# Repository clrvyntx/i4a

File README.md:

# ComNetAR: ESP32 Ring Network Connection Project

## Project Overview

This project implements a ring network topology using ESP32 microcontrollers connected via SPI (Serial Peripheral Interface). Each ESP32 board functions simultaneously as an SPI master and slave, creating a circular communication chain where data can flow bidirectionally through the network. This architecture enables efficient local communication within IoT nodes, supporting configurations from 2 to 5 boards in a single ring.

The system's unique feature is its dual-role approach: each board acts as a master for the next board and a slave for the previous one, enabling seamless data transmission throughout the network. One of the boards serves as an Access Point (AP), allowing the node to communicate with external networks while maintaining internal ring communication.

## Compatible Hardware
This project has been tested and verified to work with the following ESP32 boards:

- Espressif ESP32-DevKitC v4 (https://docs.espressif.com/projects/esp-idf/en/v5.1/esp32/hw-reference/esp32/get-started-devkitc.html#)

### Pinout

While the project may work with other ESP32 boards that have similar specifications, compatibility cannot be guaranteed without testing.

## Prerequisites

### ESP-IDF Installation
Before starting with this project, you need to install ESP-IDF v5.1.2. Follow these steps:

1. **Windows Installation**:
   - Download the ESP-IDF Windows Installer from the official ESP-IDF Releases page
   - Run the installer and follow the installation wizard
   - The installer will download and install:
     * ESP-IDF tools
     * Git
     * Python
     * Required build tools

2. **Linux/macOS Installation**:
   ```bash
   mkdir -p ~/esp
   cd ~/esp
   git clone -b v5.1.2 --recursive https://github.com/espressif/esp-idf.git
   cd esp-idf
   ./install.sh
   ```

3. **Set up ESP-IDF environment variables**:
   - Windows: Run `C:\esp\esp-idf\export.bat`
   - Linux/macOS: `. ~/esp/esp-idf/export.sh`

For detailed installation instructions, visit [ESP-IDF Get Started Guide](https://docs.espressif.com/projects/esp-idf/en/v5.1.2/esp32/get-started/index.html)

## Installing and Building the Project

1. Clone this repo and cd into it:
   ```bash
   git clone https://github.com/clrvyntx/i4a
   cd i4a
   ```

2. Set up the ESP-IDF environment:
   ```bash
   get_idf
   ```

3. Build the project:
   ```bash
   idf.py build
   ```
   Note: Initial build will take some time while it compiles all required libraries.

## Board Configuration Options

The system supports between 2 to 5 ESP32 boards in a ring configuration:

### Possible Setups:
1. **2 boards**: Minimal configuration
   - Each ESP32 acts as both master and slave
   - Direct bidirectional communication

2. **3-4 boards**: Intermediate configuration

   Forms a ring where each board connects to its neighbors
   Required boards:

   One AP (Access Point) board
   Two or three boards from: North, South, East, or West

   Example (3 boards): AP + North + South
   Example (4 boards): AP + North + South + East

3. **5 boards**: Full configuration
   - Complete board setup with all roles:
     * North board
     * South board
     * East board
     * West board
     * AP (Access Point) board

### Board Roles
Each ESP32 in the ring must be configured with its specific role using the configuration pins (see GPIO Configuration section).

## GPIO - Connections for ESP32 - Physical ports ring connections

```
Master Device          Slave Device
-------------         -------------
GPIO 23 (MOSI)  ────► GPIO 13 (MOSI)
GPIO 18 (SCLK)  ────► GPIO 14 (SCLK)
GPIO 5  (CS)    ────► GPIO 15 (CS)
```

#### Role Configuration System
**Configuration Pins (Pull-Up):**
- CONFIG_PIN_0: GPIO 22 (least significant bit)
- CONFIG_PIN_1: GPIO 21
- CONFIG_PIN_2: GPIO 16 (most significant bit)

## IDF configuration: sdkconfig file

```bash
   get_idf menuconfig
```

Variables:
```
CONFIG_LWIP_L2_TO_L3_COPY=y (Enable copy between Layer2 and Layer3 packets)
CONFIG_LWIP_IP_FORWARD=y (Enable IP forwarding)
LWIP_IP_DEBUG=y (Only for debug)
```

## ESP32 Component Testing Guide

This guide explains how to add unit tests to your ESP32 component and how to run them using the ESP-IDF unit testing framework.

### Adding Tests to Your Component

1. Create a `test` directory in your component folder:

   ```
   your_component/
   ├── include/
   ├── your_component.c
   ├── CMakeLists.txt
   └── test/
       ├── test_your_component.c
       └── CMakeLists.txt
   ```

2. Write your test cases in `test_your_component.c`:

   ```c
   #include "unity.h"
   #include "your_component.h"

   TEST_CASE("Test case description", "[your_component]")
   {
       // Your test code here
       TEST_ASSERT_EQUAL(expected, your_function());
   }
   ```

3. Create a `CMakeLists.txt` file in the `test` directory:

   ```cmake
   idf_component_register(SRC_DIRS "."
                          INCLUDE_DIRS "."
                          REQUIRES your_component unity)
   ```

### Modifying the Unit Test App

1. Navigate to the unit test app directory:

   ```
   cd $IDF_PATH/tools/unit-test-app
   ```

2. Modify the `CMakeLists.txt` file to include your component's directory:

   ```cmake
   list(APPEND EXTRA_COMPONENT_DIRS "/path/to/your/components/directory")
   ```

   Replace `/path/to/your/components/directory` with the actual path to your components.

### Running the Tests

1. Navigate to the unit test app directory:

   ```
   cd $IDF_PATH/tools/unit-test-app
   ```

2. Configure the project:

   ```
   idf.py menuconfig
   ```

   Ensure that "Component config" -> "Unity unit testing library" -> "Enable unit tests" is enabled.

3. Build the unit test app:

   ```
   idf.py -T build all build
   ```
   or 

   ```
   idf.py -T build your_component build
   ```

4. Flash the app to your ESP32:

   ```
   idf.py -p PORT flash
   ```

   Replace `PORT` with your ESP32's port (e.g., `/dev/ttyUSB0`).

5. Run the tests:

   ```
   idf.py -p PORT monitor
   ```

   In the monitor, press 't' to see the test menu and select your tests to run.

## Further Reading

For more detailed information on ESP-IDF's build system and component structure, refer to the official ESP-IDF Programming Guide:

- [ESP-IDF Build System](https://docs.espressif.com/projects/esp-idf/en/stable/esp32/api-guides/build-system.html#cmake-file-globbing)
- [Unit Testing in ESP32](https://docs.espressif.com/projects/esp-idf/en/latest/esp32/api-guides/unit-tests.html)

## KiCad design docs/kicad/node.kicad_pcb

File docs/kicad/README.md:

# Espressif KiCad Library
Download and install Espressif Library on KiCAD following the instructions in https://github.com/espressif/kicad-libraries

# Layout

## Node

## Access Poimt

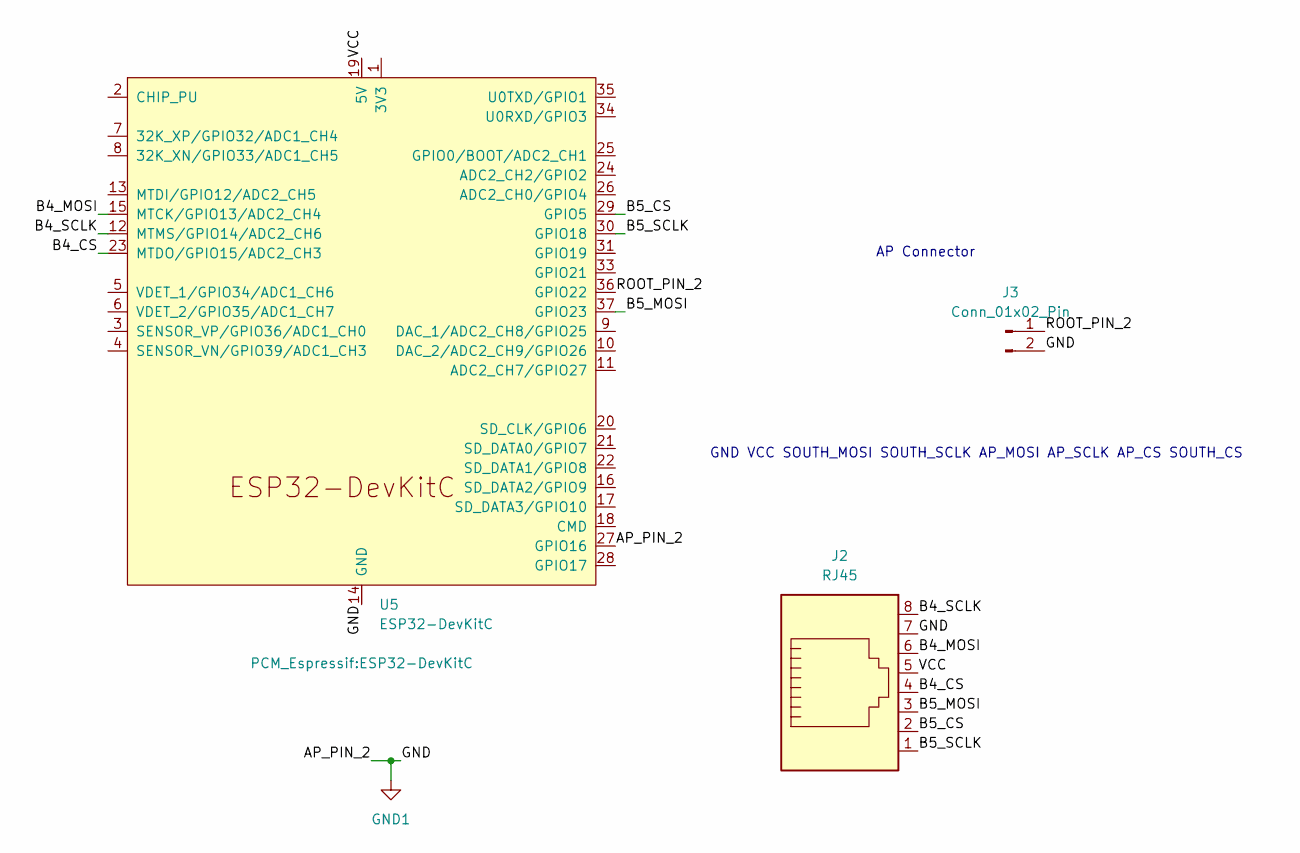
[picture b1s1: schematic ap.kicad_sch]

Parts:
J2: RJ45; RJ45_Amphenol_RJMG1BD3B8K1ANR
J3: Conn_01x02_Pin; PinHeader_1x02_P2.54mm_Vertical
U5: ESP32-DevKitC

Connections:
/ap/B4_CS: J2.4, U5.23 (MTDO/GPIO15/ADC2_CH3)
/ap/B4_MOSI: J2.6, U5.15 (MTCK/GPIO13/ADC2_CH4)
/ap/B4_SCLK: J2.8, U5.12 (MTMS/GPIO14/ADC2_CH6)
/ap/B5_CS: J2.2, U5.29 (GPIO5)
/ap/B5_MOSI: J2.3, U5.37 (GPIO23)
/ap/B5_SCLK: J2.1, U5.30 (GPIO18)
/ap/ROOT_PIN_2: J3.1, U5.36 (GPIO22)
/ap/VCC: J2.5, U5.19 (5V)
GND1: J2.7, J3.2, U5.14 (GND), U5.27 (GPIO16), U5.32 (GND), U5.38 (GND)

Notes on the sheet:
AP Connector
GND VCC SOUTH_MOSI SOUTH_SCLK AP_MOSI AP_SCLK AP_CS SOUTH_CS

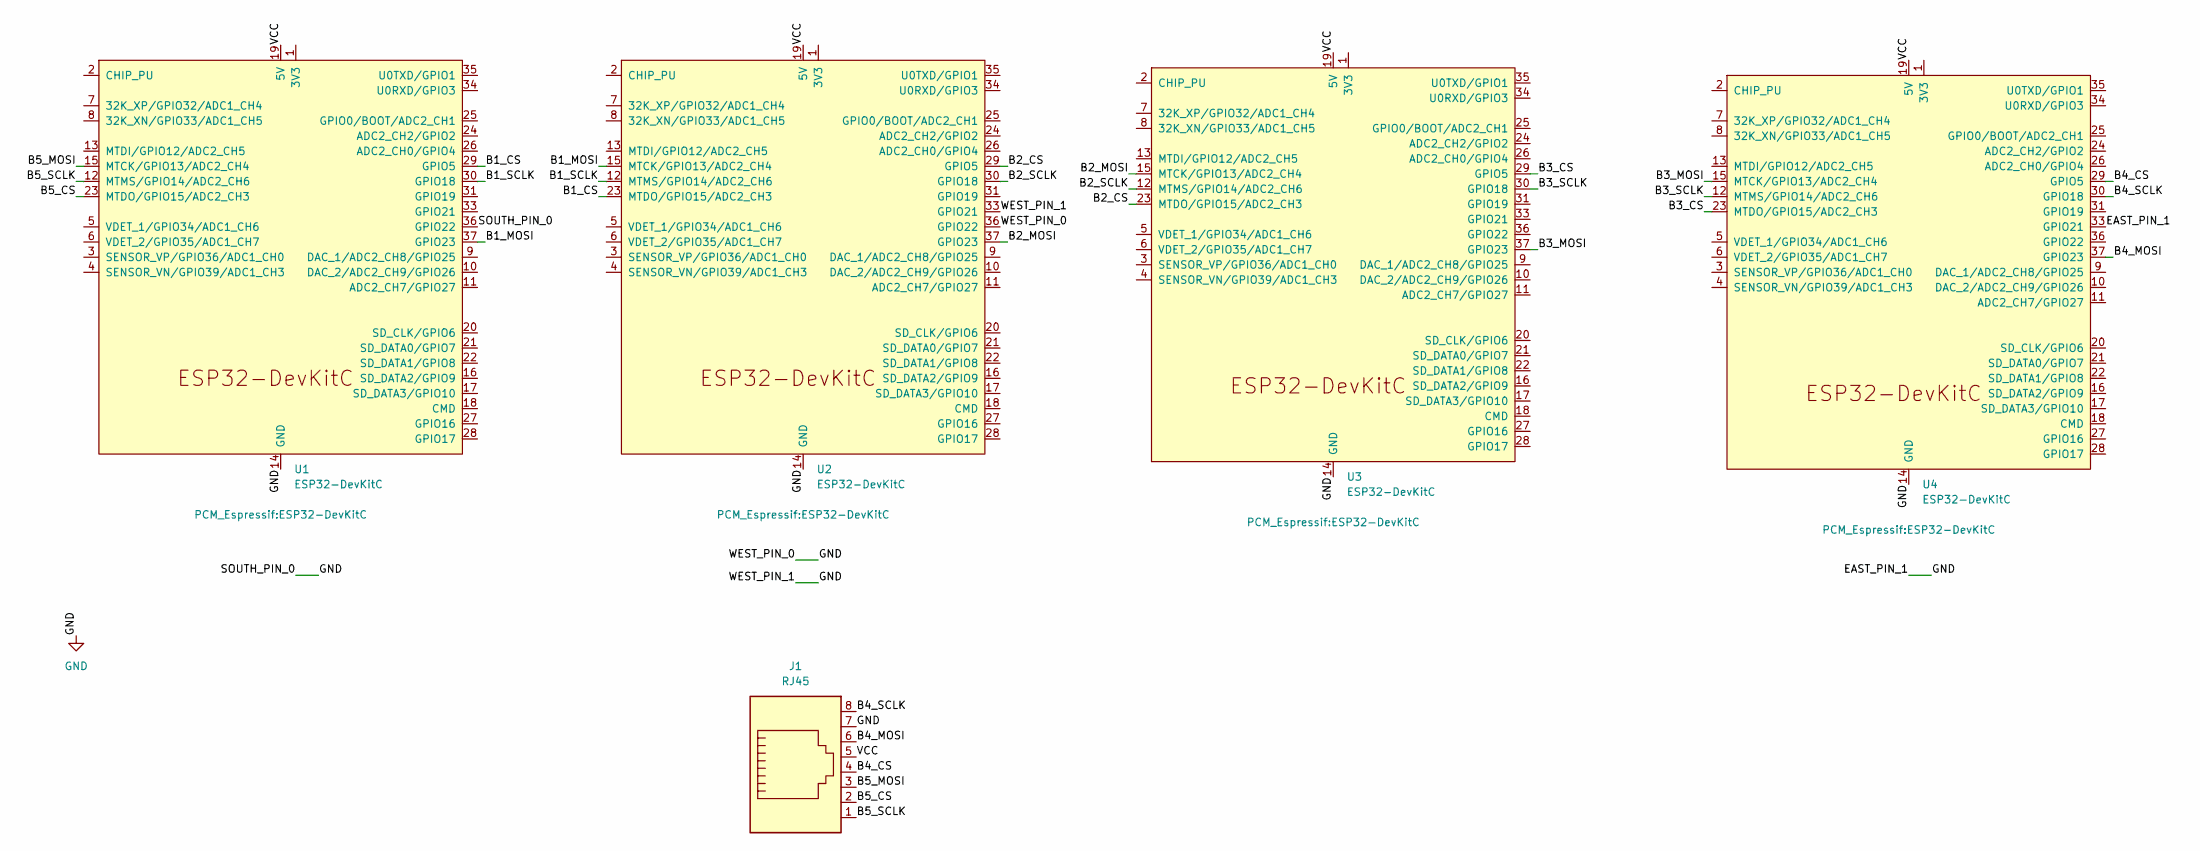
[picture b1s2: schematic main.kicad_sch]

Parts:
J1: RJ45; RJ45_Amphenol_RJMG1BD3B8K1ANR
U1, U2, U3, U4: ESP32-DevKitC

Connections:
/main/B1_CS: U1.29 (GPIO5), U2.23 (MTDO/GPIO15/ADC2_CH3)
/main/B1_MOSI: U1.37 (GPIO23), U2.15 (MTCK/GPIO13/ADC2_CH4)
/main/B1_SCLK: U1.30 (GPIO18), U2.12 (MTMS/GPIO14/ADC2_CH6)
/main/B2_CS: U2.29 (GPIO5), U3.23 (MTDO/GPIO15/ADC2_CH3)
/main/B2_MOSI: U2.37 (GPIO23), U3.15 (MTCK/GPIO13/ADC2_CH4)
/main/B2_SCLK: U2.30 (GPIO18), U3.12 (MTMS/GPIO14/ADC2_CH6)
/main/B3_CS: U3.29 (GPIO5), U4.23 (MTDO/GPIO15/ADC2_CH3)
/main/B3_MOSI: U3.37 (GPIO23), U4.15 (MTCK/GPIO13/ADC2_CH4)
/main/B3_SCLK: U3.30 (GPIO18), U4.12 (MTMS/GPIO14/ADC2_CH6)
/main/B4_CS: J1.4, U4.29 (GPIO5)
/main/B4_MOSI: J1.6, U4.37 (GPIO23)
/main/B4_SCLK: J1.8, U4.30 (GPIO18)
/main/B5_CS: J1.2, U1.23 (MTDO/GPIO15/ADC2_CH3)
/main/B5_MOSI: J1.3, U1.15 (MTCK/GPIO13/ADC2_CH4)
/main/B5_SCLK: J1.1, U1.12 (MTMS/GPIO14/ADC2_CH6)
/main/VCC: J1.5, U1.19 (5V), U2.19 (5V), U3.19 (5V), U4.19 (5V)
GND: J1.7, U1.14 (GND), U1.32 (GND), U1.36 (GPIO22), U1.38 (GND), U2.14 (GND), U2.32 (GND), U2.33 (GPIO21), U2.36 (GPIO22), U2.38 (GND), U3.14 (GND), U3.32 (GND), U3.38 (GND), U4.14 (GND), U4.32 (GND), U4.33 (GPIO21), U4.38 (GND)

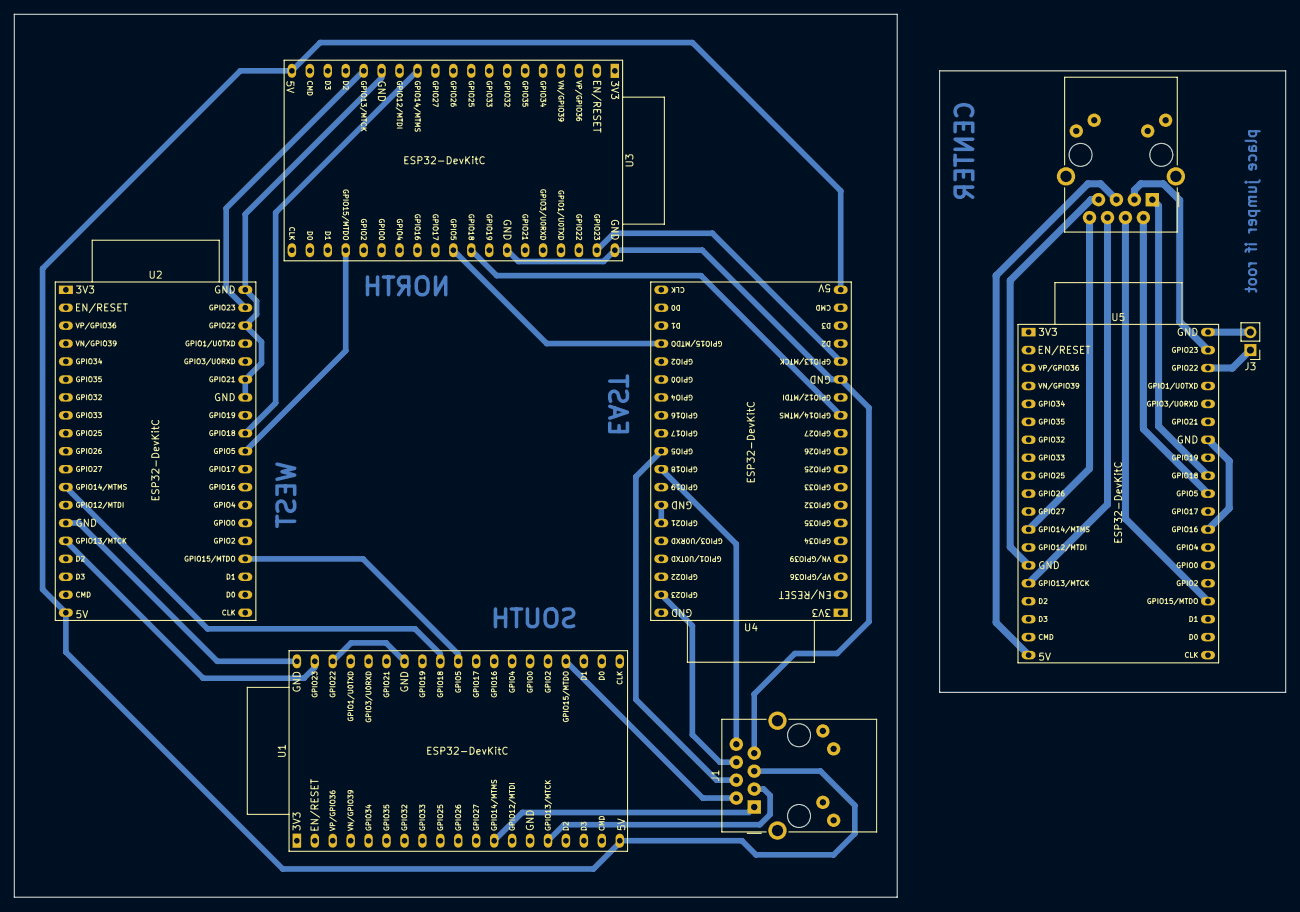
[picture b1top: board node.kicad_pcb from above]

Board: 2 copper layers, 180.0 x 125.0 mm, 8 parts (0 on the bottom side), 26 nets.

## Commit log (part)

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2025-11-29 wip: rework hal for qemu
2025-11-30 wip: wifi hal working
2025-11-30 wip: remove unused files
2025-11-30 clean up
2025-12-02 Update script
2025-12-03 ring swap
2025-12-03 ring swap routing hooks
2025-12-08 wip: pysim
2025-12-12 update pysim component
